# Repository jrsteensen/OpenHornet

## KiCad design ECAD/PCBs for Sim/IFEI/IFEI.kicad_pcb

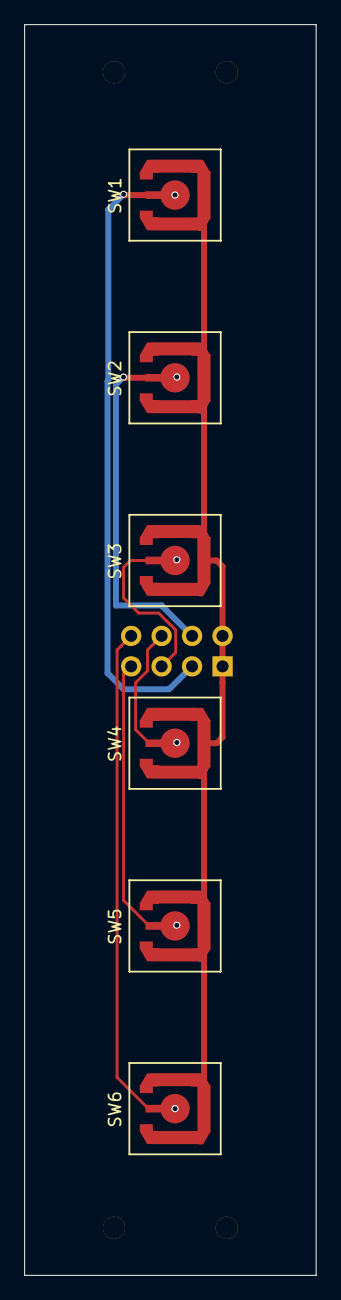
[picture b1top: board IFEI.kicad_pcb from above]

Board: 2 copper layers, 24.3 x 104.3 mm, 11 parts (1 on the bottom side), 7 nets.

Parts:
J1: Conn_02x04_Male; PinHeader_2x04_P2.54mm_Horizontal
MK1, MK2, MK3, MK4: Mounting_Hole; Mouting_Hole_1.85mm
SW1: mode; SWITCH_SNAP_DOME_6.3mm_DIA_SINGLE_SIDE_PCB
SW2: qty; SWITCH_SNAP_DOME_6.3mm_DIA_SINGLE_SIDE_PCB
SW3: up; SWITCH_SNAP_DOME_6.3mm_DIA_SINGLE_SIDE_PCB
SW4: down; SWITCH_SNAP_DOME_6.3mm_DIA_SINGLE_SIDE_PCB
SW5: zone; SWITCH_SNAP_DOME_6.3mm_DIA_SINGLE_SIDE_PCB
SW6: ET; SWITCH_SNAP_DOME_6.3mm_DIA_SINGLE_SIDE_PCB

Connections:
/A: J1.3, SW1.1
/B: J1.4, SW2.1
/C: J1.5, SW3.1
/D: J1.6, SW4.1
/E: J1.7, SW5.1
/F: J1.8, SW6.1
GND: J1.1, J1.2, SW1.2, SW2.2, SW3.2, SW4.2, SW5.2, SW6.2

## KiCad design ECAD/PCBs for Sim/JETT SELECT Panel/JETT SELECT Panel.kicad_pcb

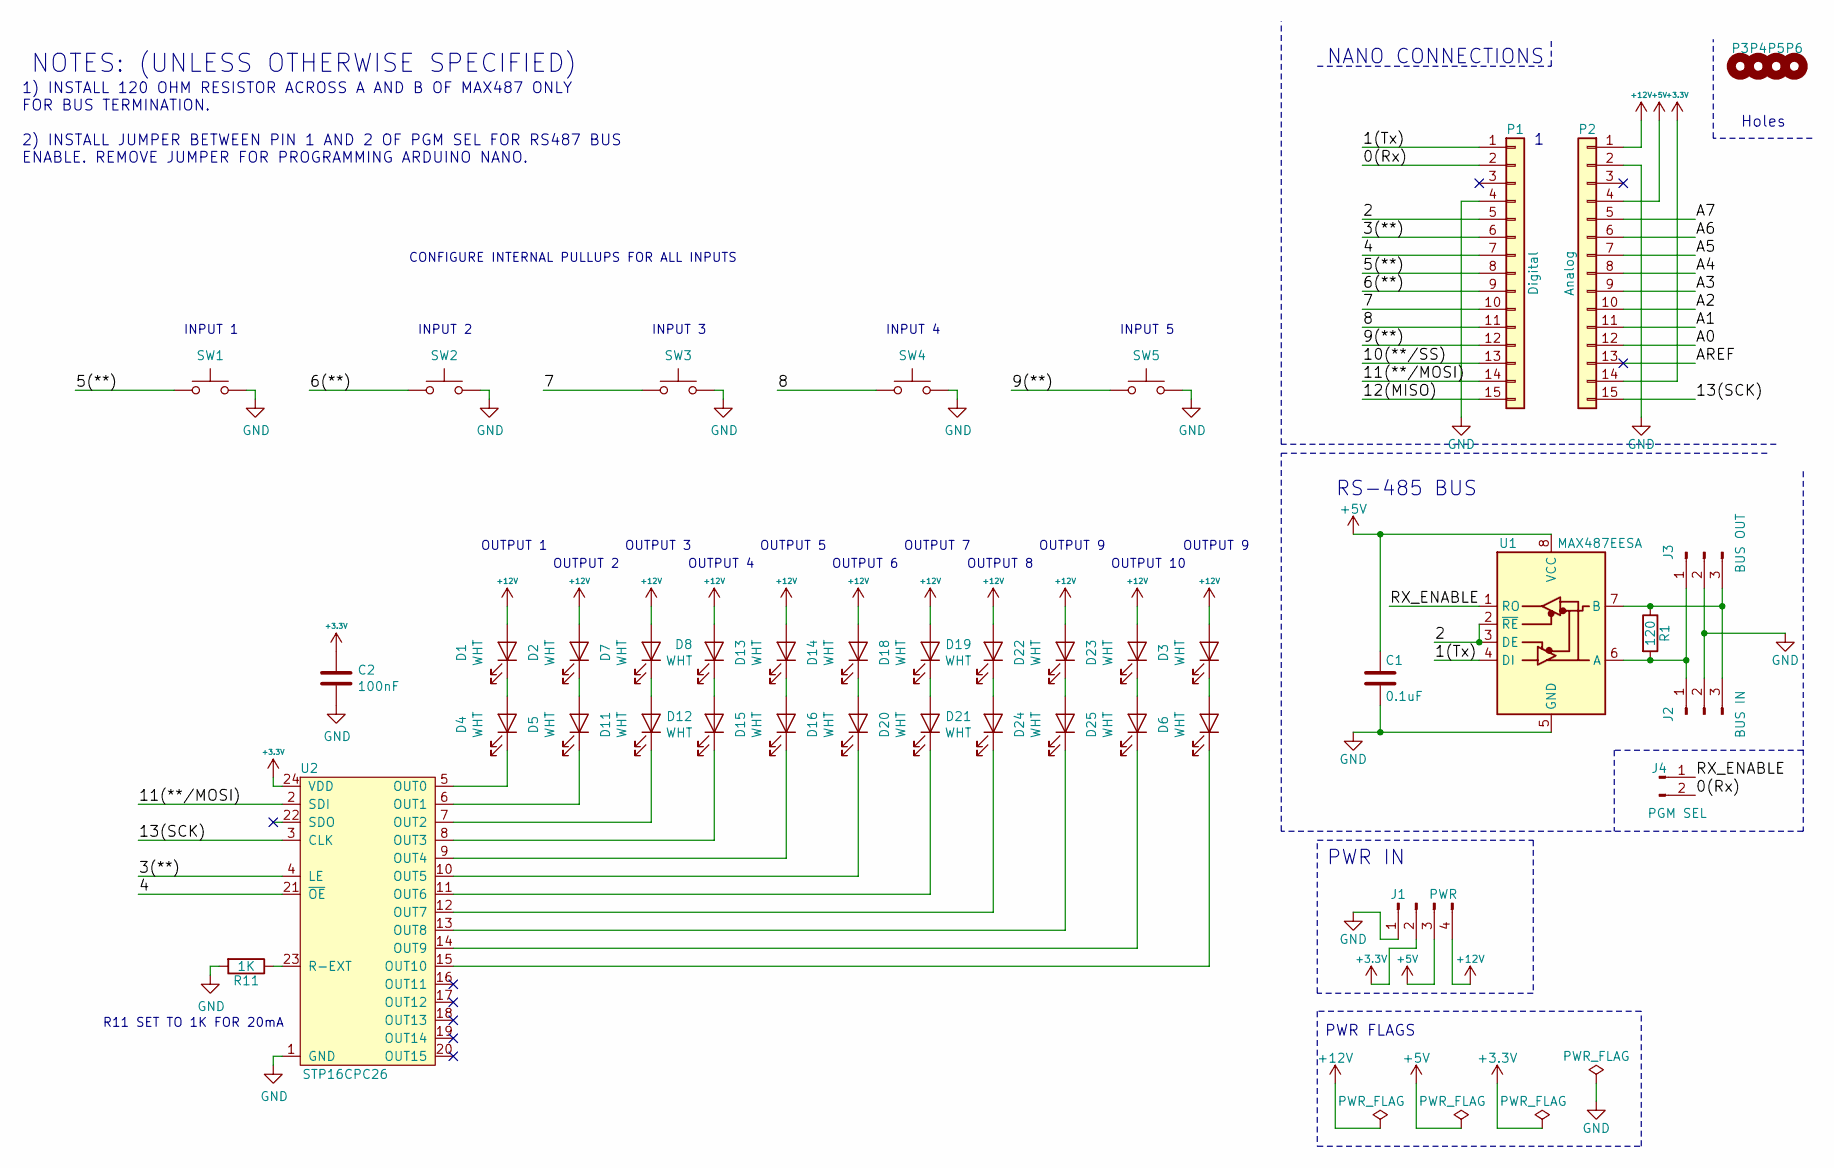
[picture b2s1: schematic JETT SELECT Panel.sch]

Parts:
C1: 0.1uF; C_0805_HandSoldering
C2: 100nF; C_0805_HandSoldering
D1, D2, D3, D4, D5, D6, D7, D8, D11, D12, D13, D14, D15, D16, D18, D19, D20, D21, D22, D23, D24, D25: WHT; LED_0603_HandSoldering
J1: PWR; Molex_KK-6410-04_04x2.54mm_Straight
J2: BUS IN; Molex_KK-6410-03_03x2.54mm_Straight
J3: BUS OUT; Molex_KK-6410-03_03x2.54mm_Straight
J4: PGM SEL; Pin_Header_Straight_1x02_Pitch2.54mm
P1: Digital; Socket_Strip_Straight_1x15_Pitch2.54mm
P2: Analog; Socket_Strip_Straight_1x15_Pitch2.54mm
P3, P4, P5, P6: CONN_01X01; MountingHole_4.3mm_M4
R1: 120; R_0805_HandSoldering
R11: 1K; R_0805_HandSoldering
SW1, SW2, SW3, SW4, SW5: SW_Push; SWITCH_SNAP_DOME_6.3mm_DIA_SINGLE_SIDE_PCB
U1: MAX487EESA; Texas_S-PWSON-N10
U2: STP16CPC26; SOIC-24W_7.5x15.4mm_Pitch1.27mm

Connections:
+3V3: C2.1, J1.2, P2.14, U2.24 (VDD)
+5V: C1.1, J1.3, P2.4, U1.8 (VCC)
+12V: D1.2 (A), D2.2 (A), D3.2 (A), D7.2 (A), D8.2 (A), D13.2 (A), D14.2 (A), D18.2 (A), D19.2 (A), D22.2 (A), D23.2 (A), J1.4, P2.1
/0(Rx): J4.2, P1.2
/1(Tx): P1.1, U1.4 (DI)
/2: P1.5, U1.2 (~RE), U1.3 (DE)
/3(**): P1.6, U2.4 (LE)
/4: P1.7, U2.21 (~OE)
/5(**): P1.8, SW1.1
/6(**): P1.9, SW2.1
/7: P1.10, SW3.1
/8: P1.11, SW4.1
/9(**): P1.12, SW5.1
/10(**/SS): P1.13
/11(**/MOSI): P1.14, U2.2 (SDI)
/12(MISO): P1.15
/13(SCK): P2.15, U2.3 (CLK)
/A0: P2.12
/A1: P2.11
/A2: P2.10
/A3: P2.9
/A4: P2.8
/A5: P2.7
/A6: P2.6
/A7: P2.5
/AREF: P2.13
/RX_ENABLE: J4.1, U1.1 (RO)
GND: C1.2, C2.2, J1.1, J2.2, J3.2, P1.4, P2.2, R11.2, SW1.2, SW2.2, SW3.2, SW4.2, SW5.2, U1.5 (GND), U2.1 (GND)
unnamed: D1.1 (K), D4.2 (A)
unnamed: D2.1 (K), D5.2 (A)
unnamed: D3.1 (K), D6.2 (A)
unnamed: D4.1 (K), U2.5 (OUT0)
unnamed: D5.1 (K), U2.6 (OUT1)
unnamed: D6.1 (K), U2.15 (OUT10)
unnamed: D11.1 (K), U2.7 (OUT2)
unnamed: D7.1 (K), D11.2 (A)
unnamed: D12.1 (K), U2.8 (OUT3)
unnamed: D8.1 (K), D12.2 (A)
unnamed: D13.1 (K), D15.2 (A)
unnamed: D14.1 (K), D16.2 (A)
unnamed: D15.1 (K), U2.9 (OUT4)
unnamed: D16.1 (K), U2.10 (OUT5)
unnamed: D18.1 (K), D20.2 (A)
unnamed: D19.1 (K), D21.2 (A)
unnamed: D20.1 (K), U2.11 (OUT6)
unnamed: D21.1 (K), U2.12 (OUT7)
unnamed: D22.1 (K), D24.2 (A)
unnamed: D23.1 (K), D25.2 (A)
unnamed: D24.1 (K), U2.13 (OUT8)
unnamed: D25.1 (K), U2.14 (OUT9)
unnamed: J2.1, J3.1, R1.2, U1.6 (A)
unnamed: J2.3, J3.3, R1.1, U1.7 (B)
unnamed: R11.1, U2.23 (R-EXT)

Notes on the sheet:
Holes
NANO CONNECTIONS
RS-485 BUS
1) INSTALL 120 OHM RESISTOR ACROSS A AND B OF MAX487 ONLY FOR BUS TERMINATION. 2) INSTALL JUMPER BETWEEN PIN 1 AND 2 OF PGM SEL FOR RS487 BUS ENABLE. REMOVE JUMPER FOR PROGRAMMING ARDUINO NANO.
NOTES: (UNLESS OTHERWISE SPECIFIED)
PWR IN
PWR FLAGS
OUTPUT 1
OUTPUT 2
OUTPUT 3
OUTPUT 4
OUTPUT 5
OUTPUT 6
OUTPUT 7
OUTPUT 8
OUTPUT 9
OUTPUT 10
INPUT 1
INPUT 2
INPUT 3
INPUT 4
INPUT 5
CONFIGURE INTERNAL PULLUPS FOR ALL INPUTS
R11 SET TO 1K FOR 20mA

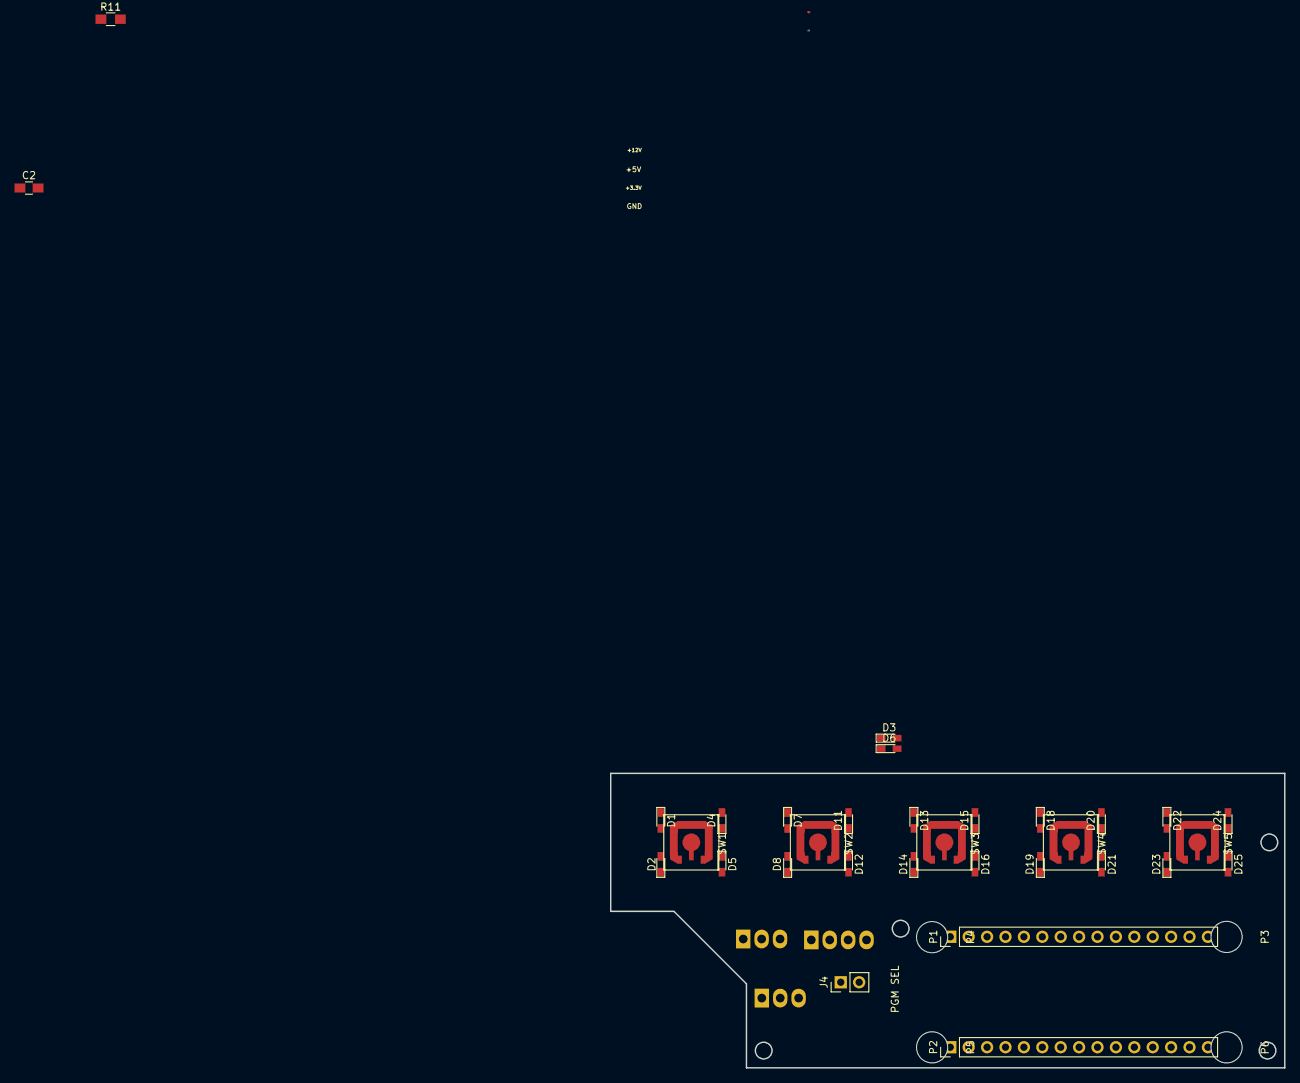
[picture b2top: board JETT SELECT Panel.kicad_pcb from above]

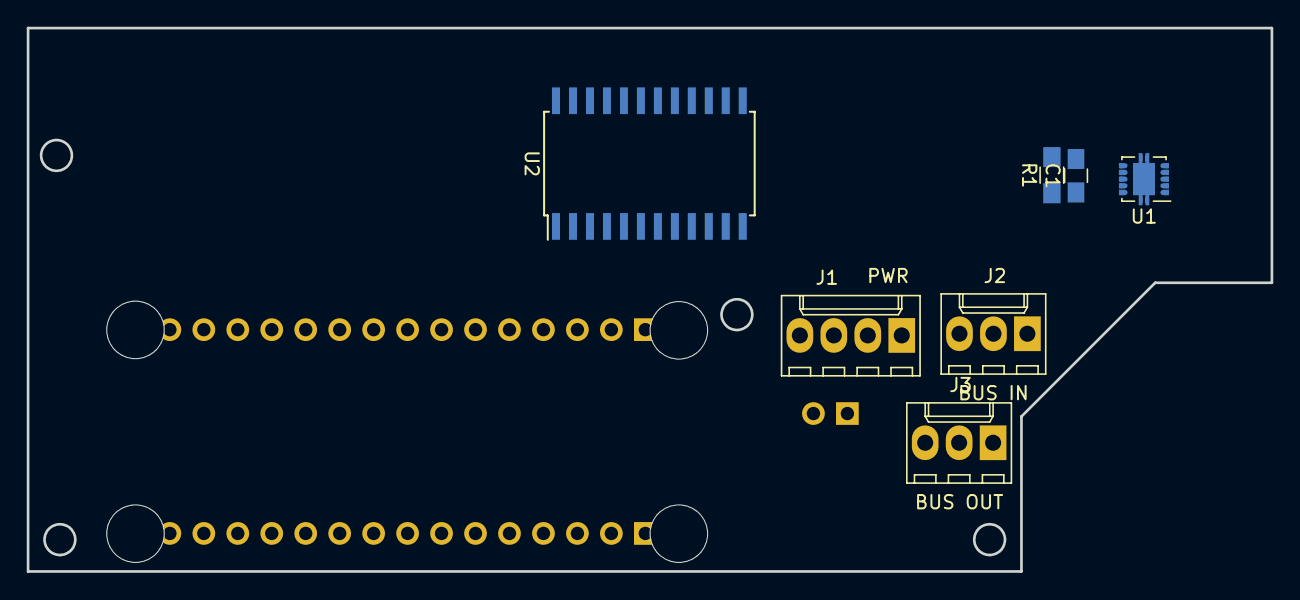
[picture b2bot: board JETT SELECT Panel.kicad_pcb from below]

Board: 2 copper layers, 93.0 x 40.6 mm, 43 parts (7 on the bottom side), 42 nets.

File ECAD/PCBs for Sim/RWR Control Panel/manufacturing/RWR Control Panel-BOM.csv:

"Id";"Designator";"Package";"Quantity";"Designation";"Supplier and ref";
1;"G***";"OH_LOGO_37.7mm_5.9mm";1;"LOGO";;;
2;"SW5,SW4,SW1,SW3,SW2";"SWITCH_SNAP_DOME_6.3mm_DIA_SINGLE_SIDE_PCB";5;"SW_Push";;;
3;"P3,P5,P4,P6";"MountingHole_2.5mm";4;"CONN_01X01";;;
4;"U1";"SOIC-8_3.9x4.9mm_P1.27mm";1;"MAX487EESA";;;
5;"J5";"Pin_Header_Straight_1x03_Pitch2.54mm";1;"RPOT1";;;
6;"J6";"Pin_Header_Straight_1x03_Pitch2.54mm";1;"RPOT2";;;
7;"J7";"Pin_Header_Straight_1x05_Pitch2.54mm";1;"5POS";;;
8;"C1";"C_0805_HandSoldering";1;"0.1uF";;;
9;"C2";"C_0805_HandSoldering";1;"100nF";;;
10;"R1";"R_0805_HandSoldering";1;"120";;;
11;"U2";"SOIC-24W_7.5x15.4mm_Pitch1.27mm";1;"STP16CPC26";;;
12;"D14,D25,D24,D23,D22,D21,D20,D19,D18,D15,D12,D11,D8,D7,D5,D4,D2,D16,D1,D13";"LED_0603_HandSoldering";20;"WHT";;;
13;"P1";"Socket_Strip_Straight_1x15_Pitch2.54mm";1;"Digital";;;
14;"P2";"Socket_Strip_Straight_1x15_Pitch2.54mm";1;"Analog";;;
15;"J4";"Pin_Header_Straight_1x02_Pitch2.54mm";1;"PGM SEL";;;
16;"J1";"Molex_KK-6410-04_04x2.54mm_Straight";1;"PWR";;;
17;"J2";"Molex_KK-6410-03_03x2.54mm_Straight";1;"BUS IN";;;
18;"J3";"Molex_KK-6410-03_03x2.54mm_Straight";1;"BUS OUT";;;

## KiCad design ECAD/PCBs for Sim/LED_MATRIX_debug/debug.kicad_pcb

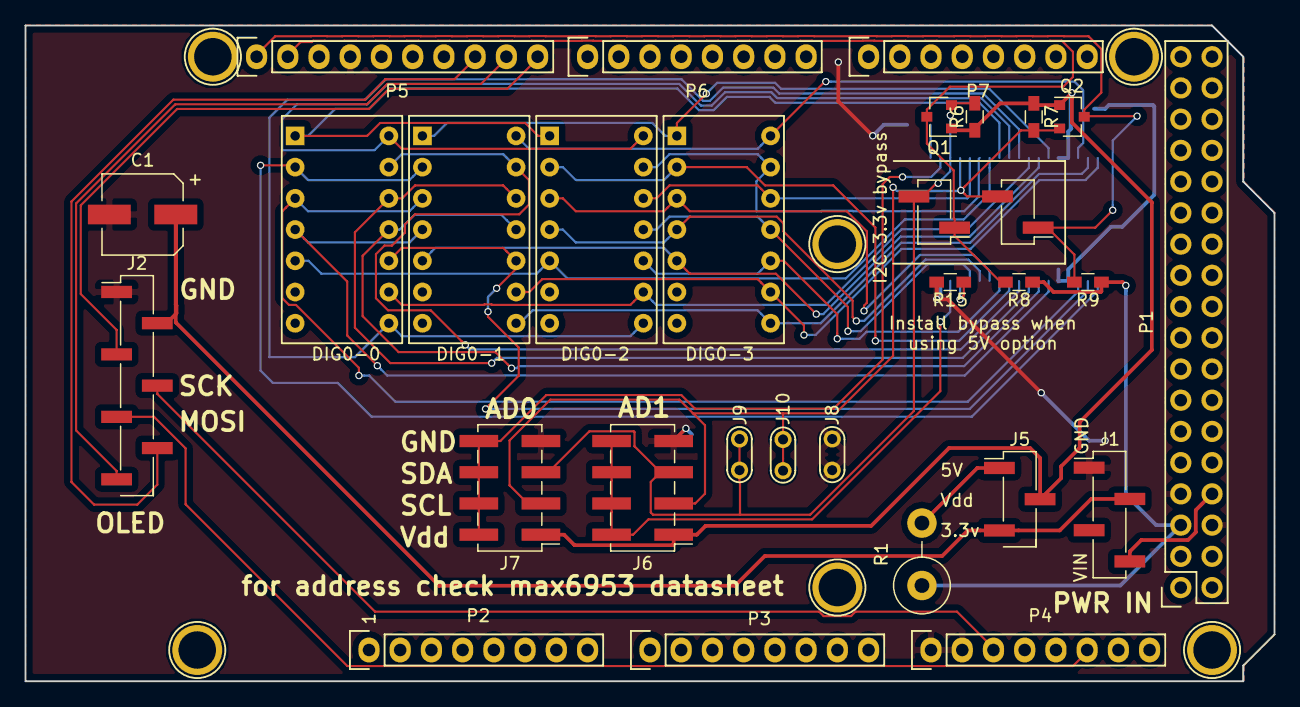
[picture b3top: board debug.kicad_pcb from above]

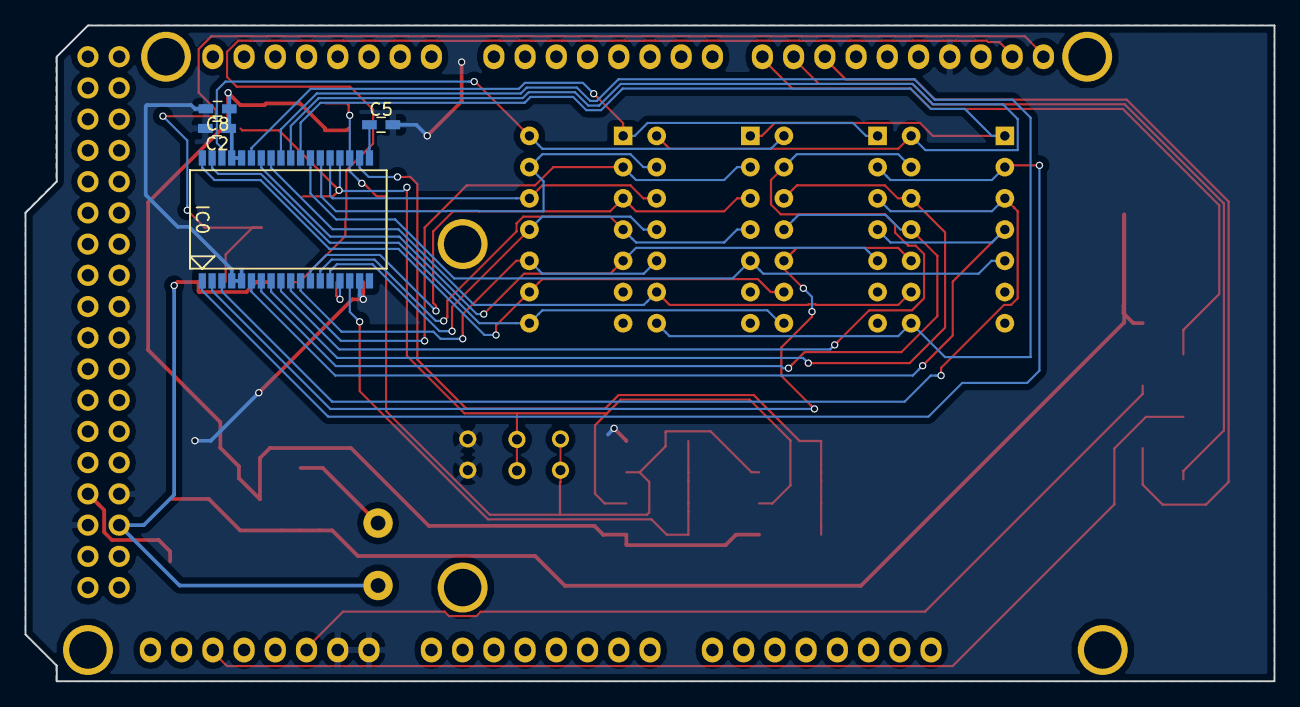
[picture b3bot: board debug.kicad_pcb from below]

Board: 2 copper layers, 101.6 x 53.3 mm, 40 parts (4 on the bottom side), 43 nets.

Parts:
C1: 220uF; CP_Elec_6.3x7.7
C2: 47uF; C_0603_HandSoldering
C5: 27pF; C_0603_HandSoldering
C8: 100nF; C_0603_HandSoldering
DIG0-0, DIG0-1, DIG0-2, DIG0-3: LTP-305G
IC0: MAX6953
J1: PWR IN; Pin_Header_Straight_1x04_Pitch2.54mm_SMD_Pin1Left
J2: OLED DISP; Pin_Header_Straight_1x07_Pitch2.54mm_SMD_Pin1Left
J3: SDA bypass; Pin_Header_Straight_1x02_Pitch2.54mm_SMD_Pin1Left
J4: SCL bypass; Pin_Header_Straight_1x02_Pitch2.54mm_SMD_Pin1Left
J5: Pwr sel; Pin_Header_Straight_1x03_Pitch2.54mm_SMD_Pin1Left
J6: ADD1; Pin_Header_Straight_2x04_Pitch2.54mm_SMD
J7: ADD0; Pin_Header_Straight_2x04_Pitch2.54mm_SMD
J8: GND; Test_Point
J9: SDA; Test_Point
J10: SCL; Test_Point
P1: Power; Socket_Strip_Arduino_2x18
P2, P3: Analog; Socket_Strip_Arduino_1x08
P4: Digital; Socket_Strip_Arduino_1x08
P5: PWM; Socket_Strip_Arduino_1x10
P6: PWM; Socket_Strip_Arduino_1x08
P7: Communication; Socket_Strip_Arduino_1x08
P8, P9, P10, P11, P12, P13: CONN_01X01; Arduino_1pin
Q1, Q2: BSS138; SOT-23
R1: 5; R_Axial_DIN0414_L11.9mm_D4.5mm_P5.08mm_Vertical
R6, R7, R8, R9: 10k; R_0603_HandSoldering
R15: 53.6k; R_0603_HandSoldering

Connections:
+3V3: C1.1, J1.2, J2.2, J5.3
+5V: P1.5, R1.1, R8.1, R9.1
/8(**): J2.3, P5.10
/9(**): J2.7, P5.9
/10(**): J2.6, P5.8
/51(MOSI): J2.5, P4.6
/52(SCK): J2.4, P4.3
/AD0: IC0.20, J7.2, J7.4, J7.6, J7.8
/AD1: IC0.16, J6.2, J6.4, J6.6, J6.8
/IC0-O0: DIG0-0.2, DIG0-1.2, IC0.1
/IC0-O1: DIG0-0.12, DIG0-1.12, IC0.2
/IC0-O2: DIG0-0.3, DIG0-1.3, IC0.3
/IC0-O3: DIG0-0.4, DIG0-1.4, IC0.6
/IC0-O4: DIG0-0.11, DIG0-1.11, IC0.7
/IC0-O5: DIG0-0.10, DIG0-1.10, IC0.8
/IC0-O6: DIG0-0.9, DIG0-1.9, IC0.9
/IC0-O7: DIG0-2.2, DIG0-3.2, IC0.10
/IC0-O8: DIG0-2.12, DIG0-3.12, IC0.11
/IC0-O9: DIG0-2.3, DIG0-3.3, IC0.12
/IC0-O10: DIG0-2.4, DIG0-3.4, IC0.13
/IC0-O11: DIG0-2.11, DIG0-3.11, IC0.14
/IC0-O12: DIG0-2.10, DIG0-3.10, IC0.23
/IC0-O13: DIG0-2.9, DIG0-3.9, IC0.24
/IC0-O14: DIG0-0.5, DIG0-2.5, IC0.25
/IC0-O15: DIG0-0.1, DIG0-2.1, IC0.26
/IC0-O16: DIG0-0.8, DIG0-2.8, IC0.27
/IC0-O17: DIG0-0.14, DIG0-2.14, IC0.28
/IC0-O18: DIG0-0.13, DIG0-2.13, IC0.29
/IC0-O19: DIG0-1.5, DIG0-3.5, IC0.30
/IC0-O20: DIG0-1.1, DIG0-3.1, IC0.31
/IC0-O21: DIG0-1.8, DIG0-3.8, IC0.34
/IC0-O22: DIG0-1.14, DIG0-3.14, IC0.35
/IC0-O23: DIG0-1.13, DIG0-3.13, IC0.36
/SCL: IC0.22, J4.2, J6.3, J7.3, J10.1, Q2.2, R7.2
/SCL5v: J4.1, P5.1, Q2.3, R9.2
/SDA: IC0.21, J3.2, J6.5, J7.5, J9.1, Q1.2, R6.2
/SDA5v: J3.1, P5.2, Q1.3, R8.2
/Vin: J1.4, P1.8
/matrixPower: C2.1, C8.1, IC0.32, IC0.33, J5.2, J6.1, J7.1, Q1.1, Q2.1, R6.1, R7.1
GND: C1.2, C2.2, C5.2, C8.2, IC0.4, IC0.5, IC0.17, J1.1, J2.1, J6.7, J7.7, J8.1, P1.6, P1.7, P4.1, P4.2, P5.4, R15.2
unnamed: C5.1, IC0.19
unnamed: IC0.15, R15.1
unnamed: J5.1, R1.2

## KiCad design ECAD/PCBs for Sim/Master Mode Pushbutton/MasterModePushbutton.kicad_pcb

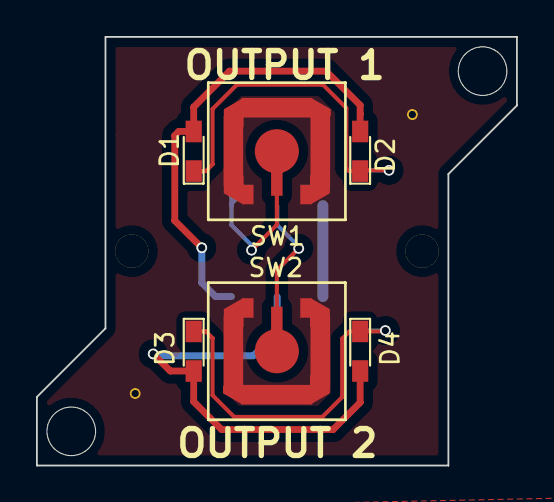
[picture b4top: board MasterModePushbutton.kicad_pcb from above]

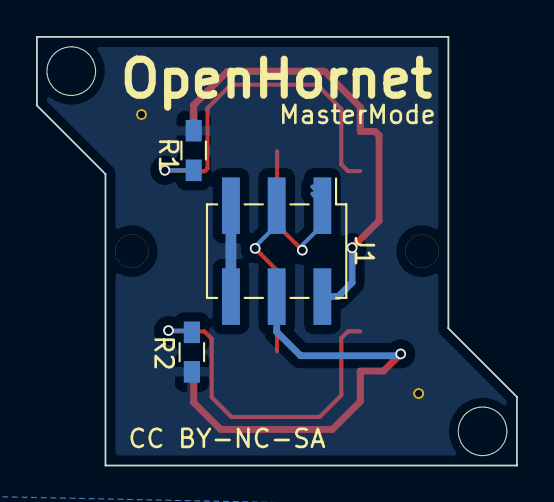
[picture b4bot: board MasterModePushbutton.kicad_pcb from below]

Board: 2 copper layers, 26.7 x 23.8 mm, 9 parts (3 on the bottom side), 7 nets.

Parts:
D1, D2, D3, D4: LED; LED_0603_HandSoldering
J1: Conn_02x03; Pin_Header_Straight_2x03_Pitch2.54mm_SMD
R1, R2: 68; R_0603_HandSoldering
SW1, SW2: push; SWITCH_SNAP_DOME_6.3mm_DIA_SINGLE_SIDE_PCB

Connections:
/backlight_1: D1.2, D2.2, J1.2
/backlight_2: D3.2, D4.2, J1.4
/switch1: J1.1, SW1.1
/switch2: J1.3, SW2.1
GND: R1.1, R2.1, SW1.2, SW2.2
unnamed: D1.1, D2.1, R1.2
unnamed: D3.1, D4.1, R2.2

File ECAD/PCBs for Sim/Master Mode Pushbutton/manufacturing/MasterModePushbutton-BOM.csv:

"Id";"Designator";"Package";"Quantity";"Designation";"Supplier and ref";
1;"REF**,REF**";"via0.6";2;"via0.6";;;
2;"REF**,REF**";"Mouting_Hole_1.85mm";2;"Mouting_Hole_1.85mm";;;
3;"D1,D2,D3,D4";"LED_0603_HandSoldering";4;"LED";;;
4;"R1,R2";"R_0603_HandSoldering";2;"68";;;
5;"SW1,SW2";"SWITCH_SNAP_DOME_6.3mm_DIA_SINGLE_SIDE_PCB";2;"push";;;
6;"J1";"Pin_Header_Straight_2x03_Pitch2.54mm_SMD";1;"Conn_02x03";;;
7;"REF**,REF**";"MountingHole_2.7mm_M2.5_ISO14580";2;"Mouting_Hole_2.71mm";;;

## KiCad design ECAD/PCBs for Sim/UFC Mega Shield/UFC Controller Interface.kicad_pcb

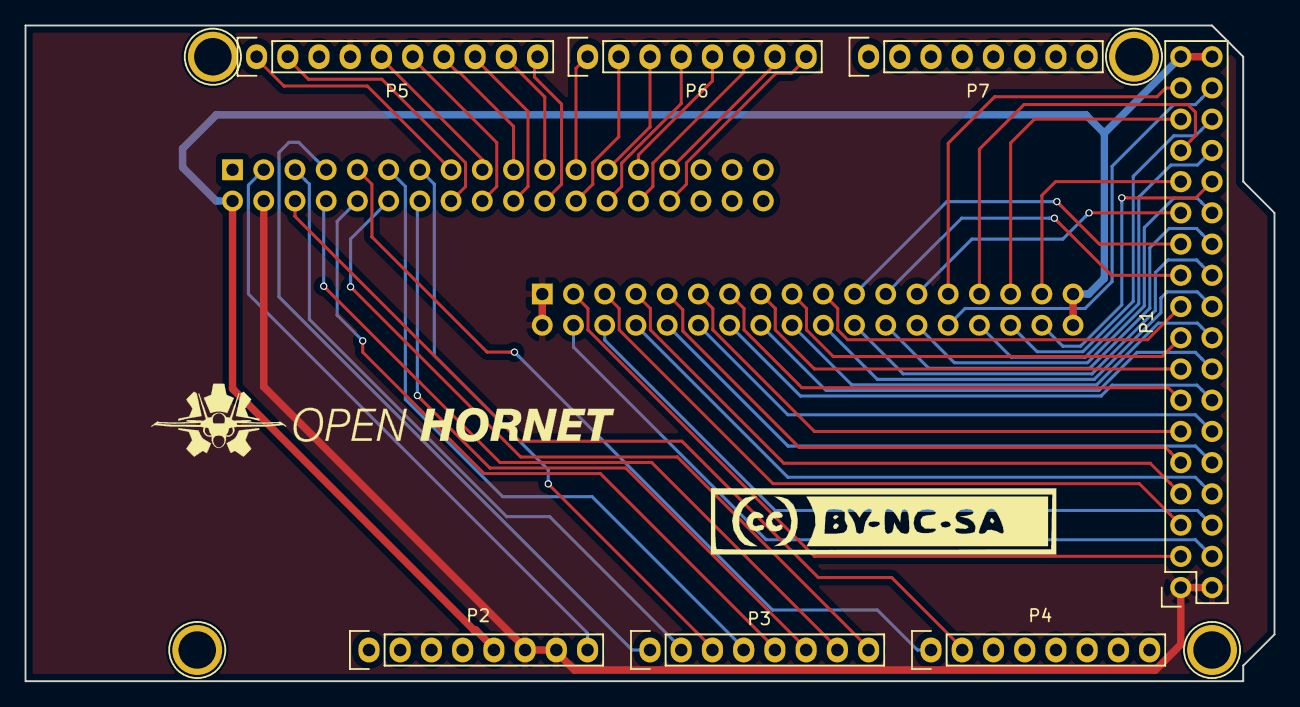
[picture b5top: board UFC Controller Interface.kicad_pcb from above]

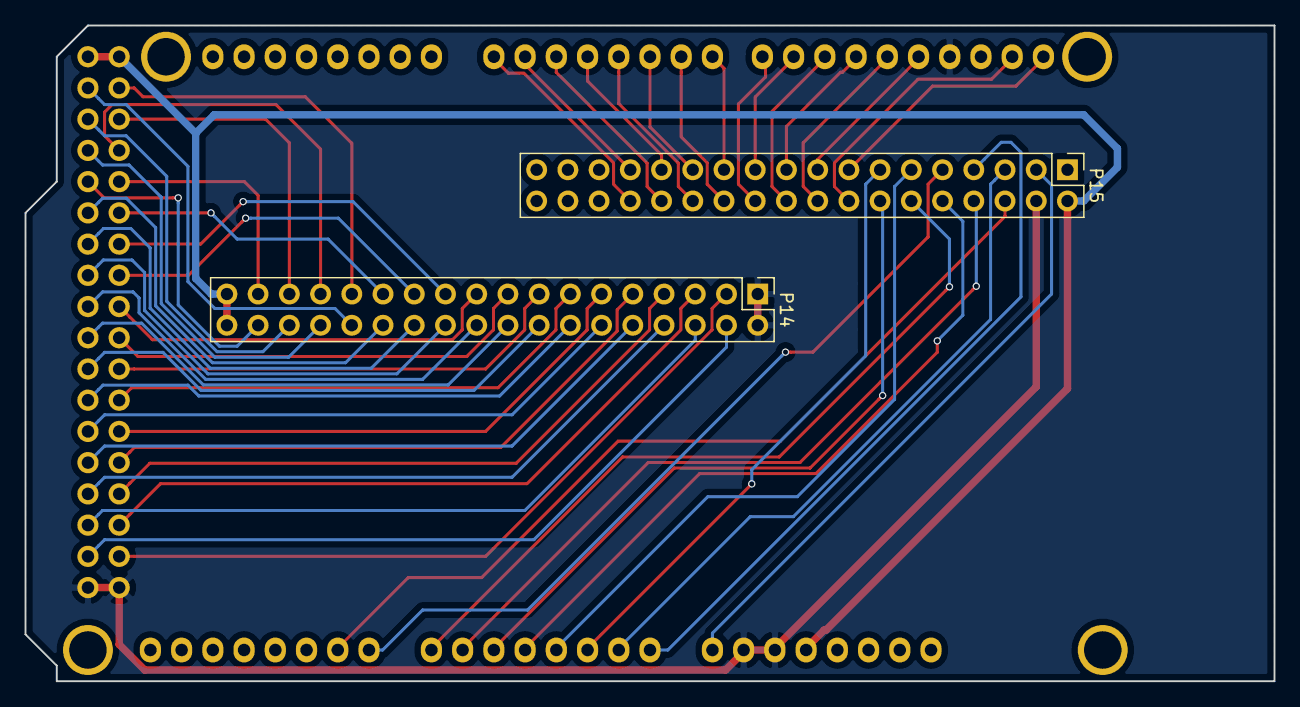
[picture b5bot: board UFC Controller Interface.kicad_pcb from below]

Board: 2 copper layers, 101.6 x 53.3 mm, 13 parts (2 on the bottom side), 61 nets.

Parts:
P1: Digital; Socket_Strip_Arduino_2x18
P2: Power; Socket_Strip_Arduino_1x08
P3, P4: Analog; Socket_Strip_Arduino_1x08
P5: PWM; Socket_Strip_Arduino_1x10
P6: PWM; Socket_Strip_Arduino_1x08
P7: Communication; Socket_Strip_Arduino_1x08
P8, P10, P11, P13: CONN_01X01; Arduino_1pin
P14: MEGA CONN 2; PinHeader_2x18_P2.54mm_Vertical
P15: MEGA CONN 1; PinHeader_2x18_P2.54mm_Vertical

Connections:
+5V: P1.35, P1.36, P2.5, P14.35, P14.36, P15.2
/0(Rx0): P6.8, P15.30
/1(Tx0): P6.7, P15.29
/2(**): P6.6, P15.28
/3(**): P6.5, P15.27
/4(**): P6.4, P15.26
/5(**): P6.3, P15.25
/6(**): P6.2, P15.24
/7(**): P6.1, P15.23
/8(**): P5.10, P15.22
/9(**): P5.9, P15.21
/10(**): P5.8, P15.20
/11(**): P5.7, P15.19
/12(**): P5.6, P15.18
/13(**): P5.5, P15.17
/22: P1.33, P14.27
/23: P1.34, P14.28
/24: P1.31, P14.31
/25: P1.32, P14.32
/26: P1.29, P14.29
/27: P1.30, P14.30
/28: P1.27, P14.33
/29: P1.28, P14.34
/30: P1.25, P14.25
/31: P1.26, P14.26
/32: P1.23, P14.21
/33: P1.24, P14.24
/34: P1.21, P14.23
/35: P1.22, P14.22
/36: P1.19, P14.19
/37: P1.20, P14.20
/38: P1.17, P14.17
/39: P1.18, P14.18
/40: P1.15, P14.15
/41: P1.16, P14.16
/42: P1.13, P14.13
/43: P1.14, P14.14
/44: P1.11, P14.11
/45: P1.12, P14.12
/46: P1.9, P14.9
/47: P1.10, P14.10
/48: P1.7, P14.7
/49: P1.8, P14.8
/50(MISO): P1.5, P14.5
/51(MOSI): P1.6, P14.6
/52(SCK): P1.3, P14.3
/53(SS): P1.4, P14.4
/A0: P3.1, P15.7
/A1: P3.2, P15.5
/A2: P3.3, P15.13
/A3: P3.4, P15.11
/A4: P3.5, P15.10
/A5: P3.6, P15.14
/A6: P3.7, P15.8
/A7: P3.8, P15.12
/A8: P4.1, P15.9
/A9: P4.2, P15.6
/SCL: P5.1, P15.15
/SDA: P5.2, P15.16
/Vin: P2.8, P15.3
GND: P1.1, P1.2, P2.6, P2.7, P5.4, P14.1, P14.2, P15.4

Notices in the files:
ECAD/PCBs for Sim/JETT SELECT Panel/JETT SELECT Panel.kicad_pcb:
CC BY-NC-SA
